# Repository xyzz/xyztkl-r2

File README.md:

# xyztkl rev2

*— Photos by [@kokaloo_](https://www.instagram.com/kokaloo_/)*

## License

CC0 apart from the switch footprints and component STEP models, see LICENSE.txt.

## Known issues

- The PCB is a bit hard to align inside the case
- The screw holes aren't at the same depth from the top

## Notes

- dboard: this uses a custom daughterboard; should be 1mm thick. JST cable or pinout **not** compatible with ai03 daughterboard
- pcb: the included PCB is using STM32F103 (or a compatible clone), you will need an ST-LINK to program the included bootloader; recommend matching the color to the color of the bottom piece if possible; should be 1.6mm thick
- jst cable: 100mm, reverse orientation (pins 1-4 on one side map to 4-1 on the other) - note that this is the opposite of what ai03 unified daughterboard uses, if you use a wrong cable you risk killing the pcb
- ALPS support: an alps-compatible PCB and plate files are provided, however they are designed to be used with the Tai Hao alps keyset and an MX spacebar; no compatibility for other layouts is provided

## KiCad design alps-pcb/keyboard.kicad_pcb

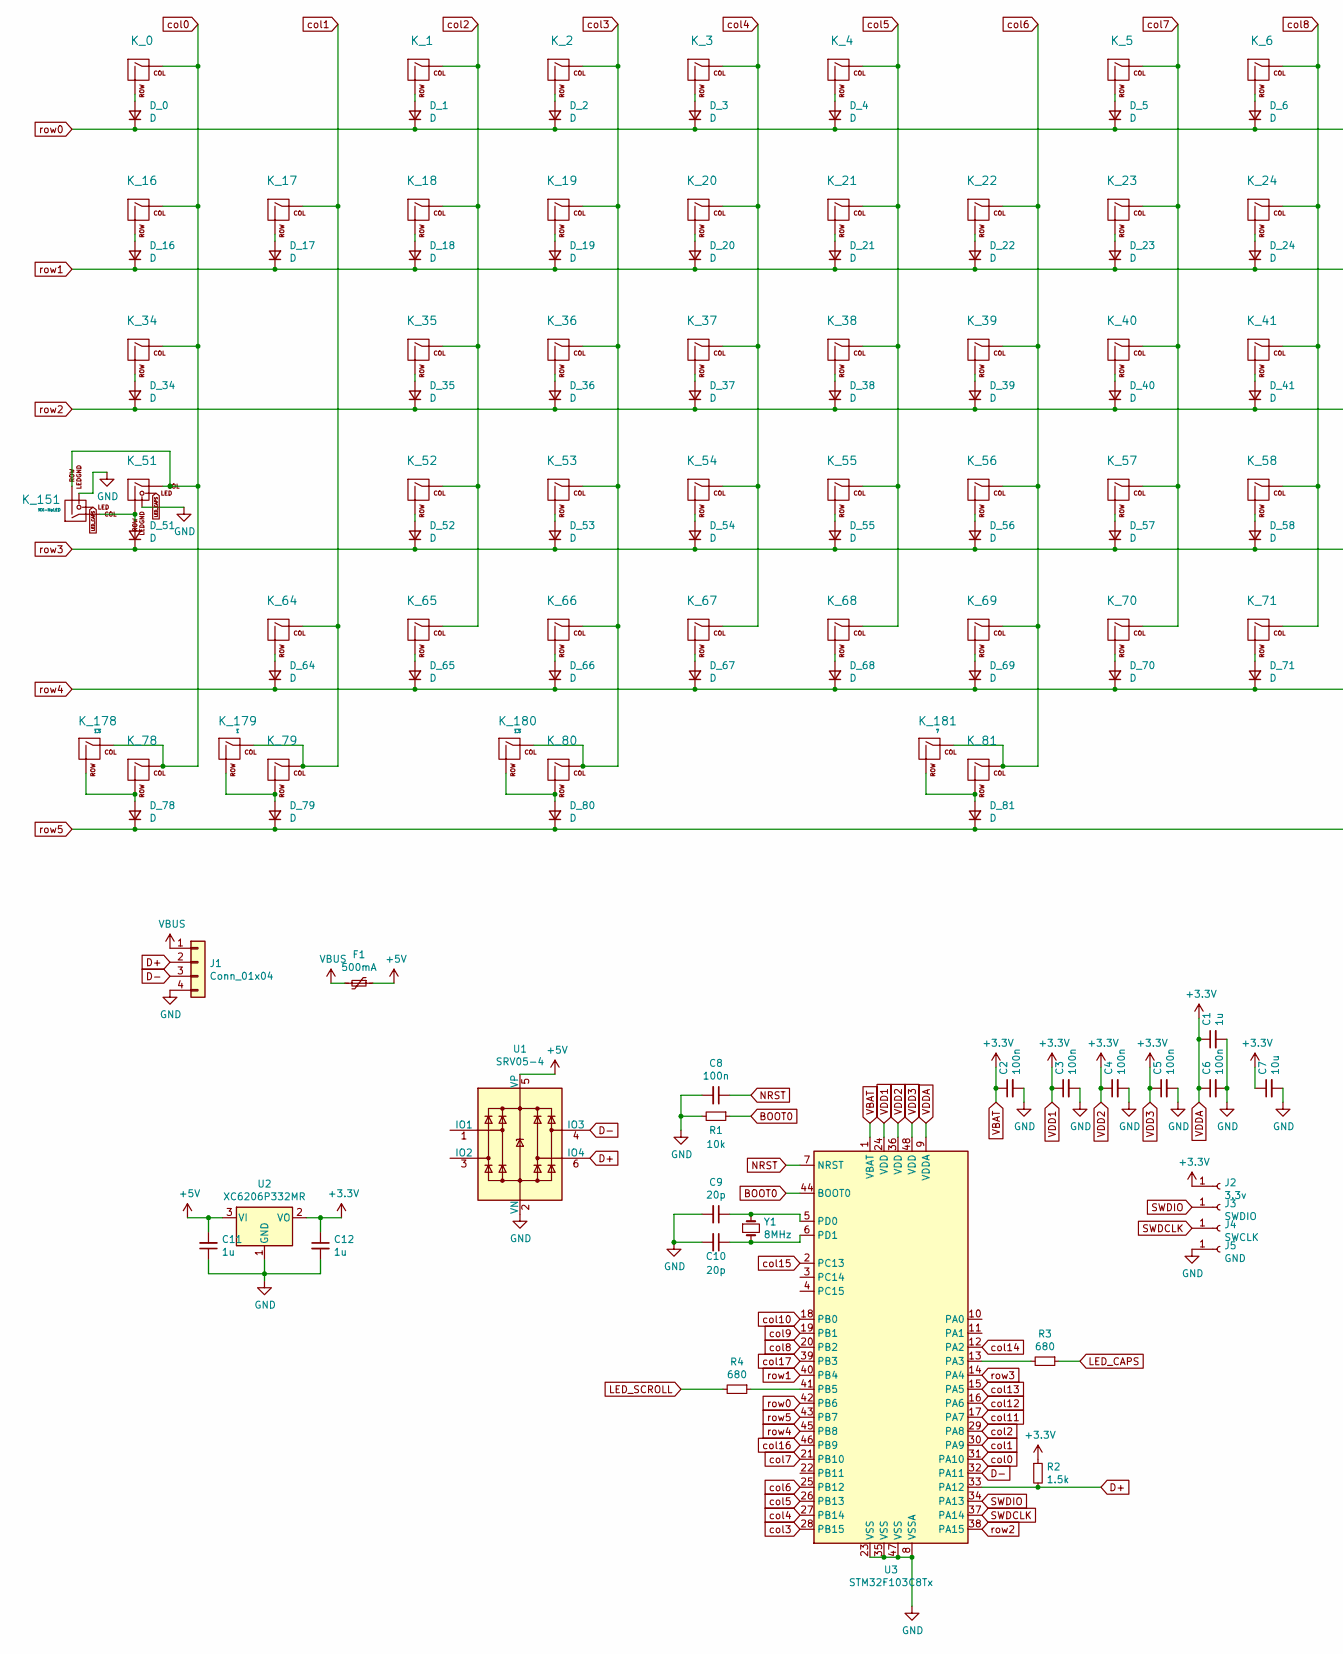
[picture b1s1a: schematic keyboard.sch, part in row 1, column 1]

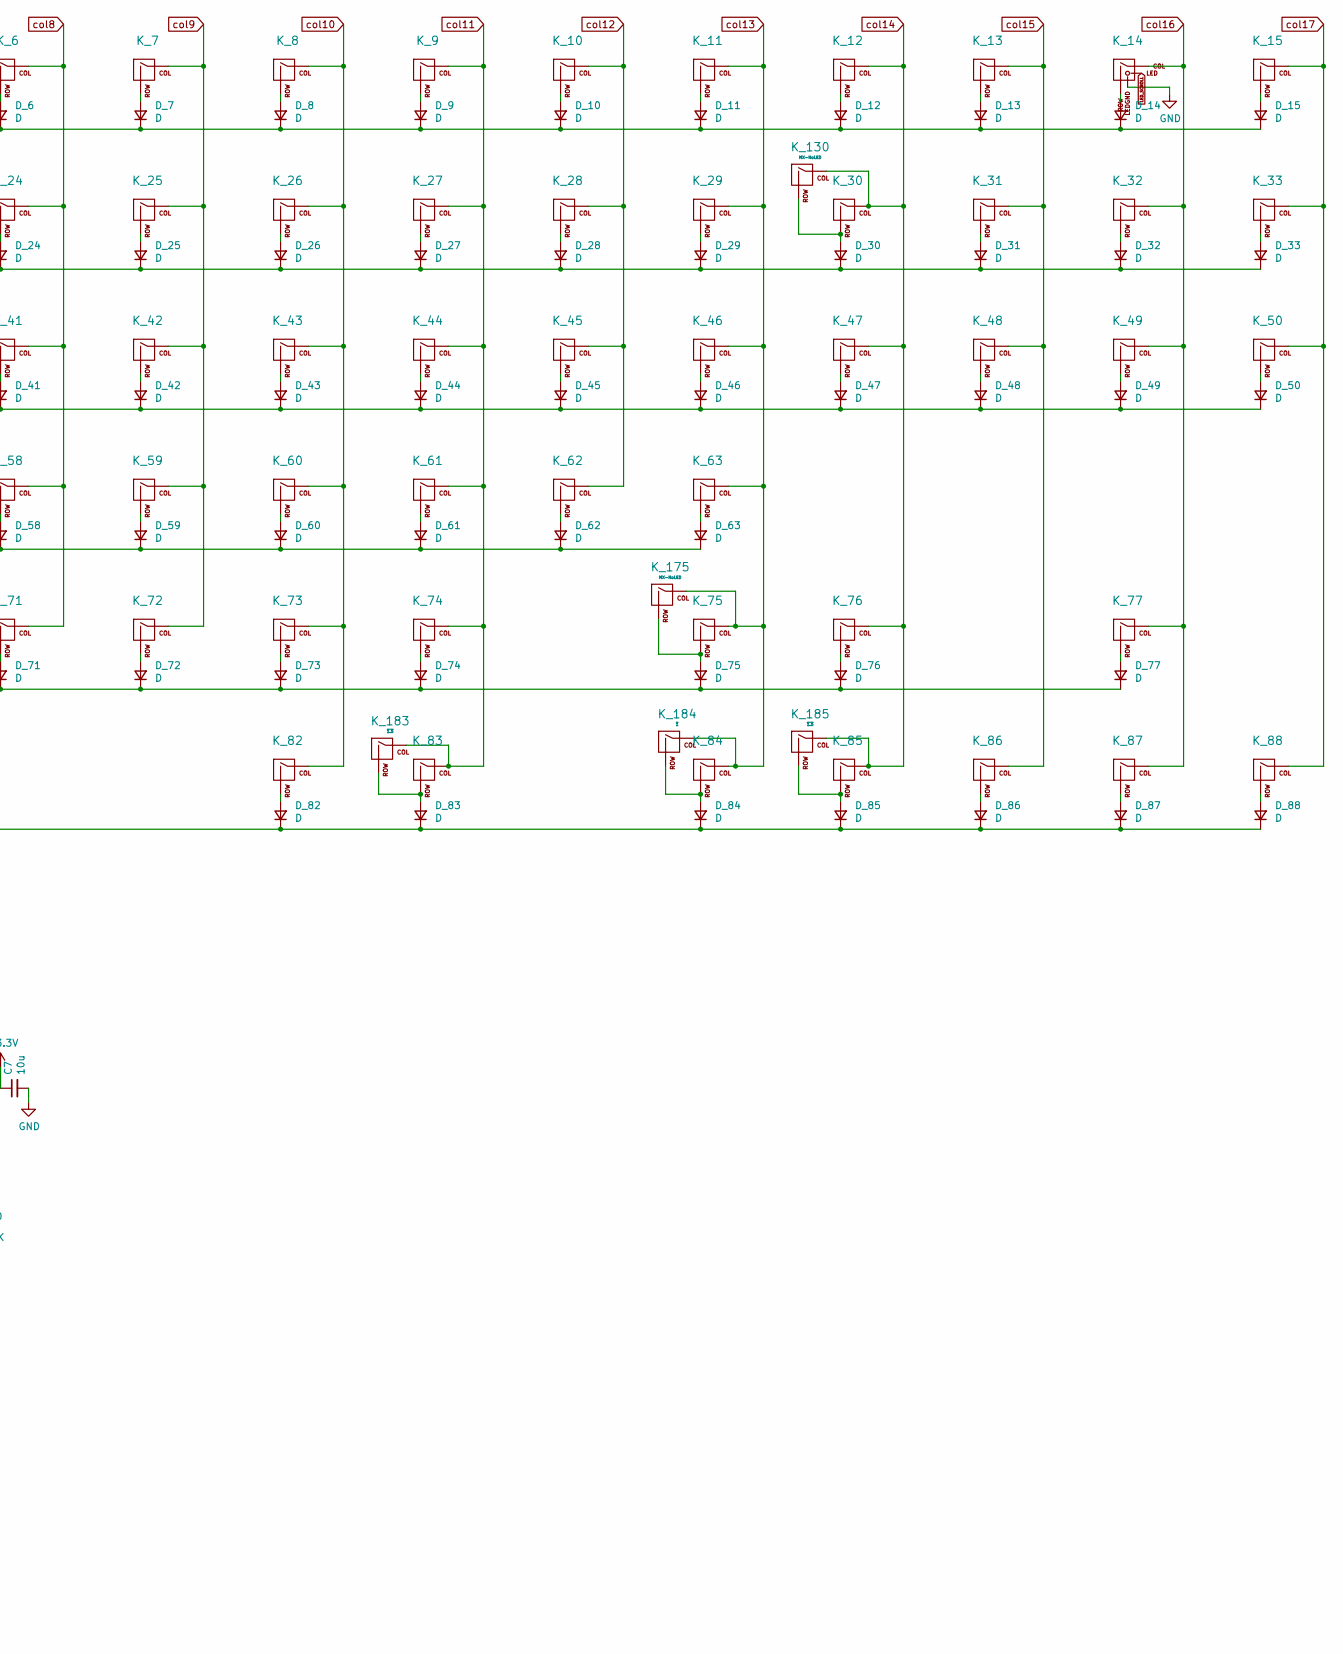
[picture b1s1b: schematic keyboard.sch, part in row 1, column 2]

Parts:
C1, C11, C12: 1u; C_0603_1608Metric; LCSC C15849
C2, C3, C4, C5, C6, C8: 100n; C_0603_1608Metric; LCSC C14663
C7: 10u; C_0603_1608Metric; LCSC C19702
C9, C10: 20p; C_0603_1608Metric; LCSC C1648
D_0, D_1, D_2, D_3, D_4, D_5, D_6, D_7, D_8, D_9, D_10, D_11, D_12, D_13, D_14, D_15, D_16, D_17, D_18, D_19, D_20, D_21, D_22, D_23, D_24, D_25, D_26, D_27, D_28, D_29, D_30, D_31, D_32, D_33, D_34, D_35, D_36, D_37, D_38, D_39, D_40, D_41, D_42, D_43, D_44, D_45, D_46, D_47, D_48, D_49, D_50, D_51, D_52, D_53, D_54, D_55, D_56, D_57, D_58, D_59, D_60, D_61, D_62, D_63, D_64, D_65, D_66, D_67, D_68, D_69, D_70, D_71, D_72, D_73, D_74, D_75, D_76, D_77, D_78, D_79, D_80, D_81, D_82, D_83, D_84, D_85, D_86, D_87, D_88: D; D_SOD-123; LCSC C81598
F1: 500mA; Fuse_1206_3216Metric; LCSC C369159
J1: Conn_01x04; JST_SH_SM04B-SRSS-TB_1x04-1MP_P1.00mm_Horizontal; LCSC C160404
J2: 3.3v; TestPoint_Pad_D1.5mm
J3: SWDIO; TestPoint_Pad_D1.5mm
J4: SWCLK; TestPoint_Pad_D1.5mm
J5: GND; TestPoint_Pad_D1.5mm
K_0, K_1, K_2, K_3, K_4, K_5, K_6, K_7, K_8, K_9, K_10, K_11, K_12, K_13, K_15, K_16, K_17, K_18, K_19, K_20, K_21, K_22, K_23, K_24, K_25, K_26, K_27, K_28, K_29, K_30, K_31, K_32, K_33, K_35, K_36, K_37, K_38, K_39, K_40, K_41, K_42, K_43, K_44, K_45, K_46, K_48, K_49, K_50, K_52, K_53, K_54, K_55, K_56, K_57, K_58, K_59, K_60, K_61, K_62, K_65, K_66, K_67, K_68, K_69, K_70, K_71, K_72, K_73, K_74, K_76, K_77, K_86, K_87, K_88: KEYSW; MX-1U-NoLED
K_14: KEYSW; MX-1U
K_34, K_47: KEYSW; MX-1.5U-NoLED
K_51: KEYSW; MX-1.75U
K_63, K_64: KEYSW; MX-2.25U-NoLED
K_75: KEYSW; MX-1.75U-NoLED
K_78, K_79, K_80, K_82, K_83, K_84, K_85: 1.25; MX-1.25U-NoLED
K_81: 6.25; MX-6.25U-ReversedStabilizers-NoLED
K_130: MX-NoLED; MX-2U-NoLED
K_151: MX-NoLED; MX-1.25U-FLIPPED
K_175: MX-NoLED; MX-2.75U-NoLED
K_178, K_180, K_183, K_185: ~1.5; MX-1.5U-NoLED
K_179, K_184: ~1; MX-1U-NoLED
K_181: ~7; MX-7U-ReversedStabilizers-NoLED
R1: 10k; R_0603_1608Metric; LCSC C25804
R2: 1.5k; R_0603_1608Metric; LCSC C22843
R3, R4: 680; R_0603_1608Metric; LCSC C23228
U1: SRV05-4; SOT-23-6; LCSC C85364
U2: XC6206P332MR; SOT-23; LCSC C5446
U3: STM32F103C8Tx; LQFP-48_7x7mm_P0.5mm
Y1: 8MHz; Crystal_SMD_5032-2Pin_5.0x3.2mm; LCSC C115962

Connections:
+5V: C11.2, F1.1, U1.5 (VP), U2.3 (VI)
BOOT0: R1.1, U3.44 (BOOT0)
D+: J1.2, R2.2, U1.6 (IO4), U3.33 (PA12)
D-: J1.3, U1.4 (IO3), U3.32 (PA11)
GND: C1.2, C2.2, C3.2, C4.2, C5.2, C6.2, C7.2, C8.2, C9.2, C10.2, C11.1, C12.2, J1.4, J5.1, K_14.4 (LEDGND), K_51.4 (LEDGND), K_151.4 (LEDGND), R1.2, U1.2 (VN), U2.1 (GND), U3.8 (VSSA), U3.23 (VSS), U3.35 (VSS), U3.47 (VSS)
LED_CAPS: K_51.3 (LED), K_151.3 (LED), R3.1
LED_SCROLL: K_14.3 (LED), R4.2
NRST: C8.1, U3.7 (NRST)
unnamed: C9.1, U3.5 (PD0), Y1.1
unnamed: C10.1, U3.6 (PD1), Y1.2
unnamed: D_0.2 (A), K_0.2 (ROW)
unnamed: D_1.2 (A), K_1.2 (ROW)
unnamed: D_2.2 (A), K_2.2 (ROW)
unnamed: D_3.2 (A), K_3.2 (ROW)
unnamed: D_4.2 (A), K_4.2 (ROW)
unnamed: D_5.2 (A), K_5.2 (ROW)
unnamed: D_6.2 (A), K_6.2 (ROW)
unnamed: D_7.2 (A), K_7.2 (ROW)
unnamed: D_8.2 (A), K_8.2 (ROW)
unnamed: D_9.2 (A), K_9.2 (ROW)
unnamed: D_10.2 (A), K_10.2 (ROW)
unnamed: D_11.2 (A), K_11.2 (ROW)
unnamed: D_12.2 (A), K_12.2 (ROW)
unnamed: D_13.2 (A), K_13.2 (ROW)
unnamed: D_14.2 (A), K_14.2 (ROW)
unnamed: D_15.2 (A), K_15.2 (ROW)
unnamed: D_16.2 (A), K_16.2 (ROW)
unnamed: D_17.2 (A), K_17.2 (ROW)
unnamed: D_18.2 (A), K_18.2 (ROW)
unnamed: D_19.2 (A), K_19.2 (ROW)
unnamed: D_20.2 (A), K_20.2 (ROW)
unnamed: D_21.2 (A), K_21.2 (ROW)
unnamed: D_22.2 (A), K_22.2 (ROW)
unnamed: D_23.2 (A), K_23.2 (ROW)
unnamed: D_24.2 (A), K_24.2 (ROW)
unnamed: D_25.2 (A), K_25.2 (ROW)
unnamed: D_26.2 (A), K_26.2 (ROW)
unnamed: D_27.2 (A), K_27.2 (ROW)
unnamed: D_28.2 (A), K_28.2 (ROW)
unnamed: D_29.2 (A), K_29.2 (ROW)
unnamed: D_30.2 (A), K_30.2 (ROW), K_130.2 (ROW)
unnamed: D_31.2 (A), K_31.2 (ROW)
unnamed: D_32.2 (A), K_32.2 (ROW)
unnamed: D_33.2 (A), K_33.2 (ROW)
unnamed: D_34.2 (A), K_34.2 (ROW)
unnamed: D_35.2 (A), K_35.2 (ROW)
unnamed: D_36.2 (A), K_36.2 (ROW)
unnamed: D_37.2 (A), K_37.2 (ROW)
unnamed: D_38.2 (A), K_38.2 (ROW)
unnamed: D_39.2 (A), K_39.2 (ROW)
unnamed: D_40.2 (A), K_40.2 (ROW)
unnamed: D_41.2 (A), K_41.2 (ROW)
unnamed: D_42.2 (A), K_42.2 (ROW)
unnamed: D_43.2 (A), K_43.2 (ROW)
unnamed: D_44.2 (A), K_44.2 (ROW)
unnamed: D_45.2 (A), K_45.2 (ROW)
unnamed: D_46.2 (A), K_46.2 (ROW)
unnamed: D_47.2 (A), K_47.2 (ROW)
unnamed: D_48.2 (A), K_48.2 (ROW)
unnamed: D_49.2 (A), K_49.2 (ROW)
unnamed: D_50.2 (A), K_50.2 (ROW)
unnamed: D_51.2 (A), K_51.2 (ROW), K_151.1 (COL)
unnamed: D_52.2 (A), K_52.2 (ROW)
unnamed: D_53.2 (A), K_53.2 (ROW)
unnamed: D_54.2 (A), K_54.2 (ROW)
unnamed: D_55.2 (A), K_55.2 (ROW)
unnamed: D_56.2 (A), K_56.2 (ROW)
unnamed: D_57.2 (A), K_57.2 (ROW)
unnamed: D_58.2 (A), K_58.2 (ROW)
unnamed: D_59.2 (A), K_59.2 (ROW)
unnamed: D_60.2 (A), K_60.2 (ROW)
unnamed: D_61.2 (A), K_61.2 (ROW)
unnamed: D_62.2 (A), K_62.2 (ROW)
unnamed: D_63.2 (A), K_63.2 (ROW)
unnamed: D_64.2 (A), K_64.2 (ROW)
unnamed: D_65.2 (A), K_65.2 (ROW)
unnamed: D_66.2 (A), K_66.2 (ROW)
unnamed: D_67.2 (A), K_67.2 (ROW)
unnamed: D_68.2 (A), K_68.2 (ROW)
unnamed: D_69.2 (A), K_69.2 (ROW)
unnamed: D_70.2 (A), K_70.2 (ROW)
unnamed: D_71.2 (A), K_71.2 (ROW)
unnamed: D_72.2 (A), K_72.2 (ROW)
unnamed: D_73.2 (A), K_73.2 (ROW)
unnamed: D_74.2 (A), K_74.2 (ROW)
unnamed: D_75.2 (A), K_75.2 (ROW), K_175.2 (ROW)
unnamed: D_76.2 (A), K_76.2 (ROW)
unnamed: D_77.2 (A), K_77.2 (ROW)
unnamed: D_78.2 (A), K_78.2 (ROW), K_178.2 (ROW)
unnamed: D_79.2 (A), K_79.2 (ROW), K_179.2 (ROW)
unnamed: D_80.2 (A), K_80.2 (ROW), K_180.2 (ROW)
unnamed: D_81.2 (A), K_81.2 (ROW), K_181.2 (ROW)
unnamed: D_82.2 (A), K_82.2 (ROW)
unnamed: D_83.2 (A), K_83.2 (ROW), K_183.2 (ROW)
unnamed: D_84.2 (A), K_84.2 (ROW), K_184.2 (ROW)
unnamed: D_85.2 (A), K_85.2 (ROW), K_185.2 (ROW)
unnamed: D_86.2 (A), K_86.2 (ROW)
unnamed: D_87.2 (A), K_87.2 (ROW)
unnamed: D_88.2 (A), K_88.2 (ROW)
unnamed: R3.2, U3.13 (PA3)
unnamed: R4.1, U3.41 (PB5)
SWDCLK: J4.1, U3.37 (PA14)
SWDIO: J3.1, U3.34 (PA13)
VBAT: C1.1, C2.1, C3.1, C4.1, C5.1, C6.1, C7.1, C12.1, J2.1, R2.1, U2.2 (VO), U3.1 (VBAT), U3.9 (VDDA), U3.24 (VDD), U3.36 (VDD), U3.48 (VDD)
VBUS: F1.2, J1.1
col0: K_0.1 (COL), K_16.1 (COL), K_34.1 (COL), K_51.1 (COL), K_78.1 (COL), K_151.2 (ROW), K_178.1 (COL), U3.31 (PA10)
col1: K_17.1 (COL), K_64.1 (COL), K_79.1 (COL), K_179.1 (COL), U3.30 (PA9)
col2: K_1.1 (COL), K_18.1 (COL), K_35.1 (COL), K_52.1 (COL), K_65.1 (COL), U3.29 (PA8)
col3: K_2.1 (COL), K_19.1 (COL), K_36.1 (COL), K_53.1 (COL), K_66.1 (COL), K_80.1 (COL), K_180.1 (COL), U3.28 (PB15)
col4: K_3.1 (COL), K_20.1 (COL), K_37.1 (COL), K_54.1 (COL), K_67.1 (COL), U3.27 (PB14)
col5: K_4.1 (COL), K_21.1 (COL), K_38.1 (COL), K_55.1 (COL), K_68.1 (COL), U3.26 (PB13)
col6: K_22.1 (COL), K_39.1 (COL), K_56.1 (COL), K_69.1 (COL), K_81.1 (COL), K_181.1 (COL), U3.25 (PB12)
col7: K_5.1 (COL), K_23.1 (COL), K_40.1 (COL), K_57.1 (COL), K_70.1 (COL), U3.21 (PB10)
col8: K_6.1 (COL), K_24.1 (COL), K_41.1 (COL), K_58.1 (COL), K_71.1 (COL), U3.20 (PB2)
col9: K_7.1 (COL), K_25.1 (COL), K_42.1 (COL), K_59.1 (COL), K_72.1 (COL), U3.19 (PB1)
col10: K_8.1 (COL), K_26.1 (COL), K_43.1 (COL), K_60.1 (COL), K_73.1 (COL), K_82.1 (COL), U3.18 (PB0)
col11: K_9.1 (COL), K_27.1 (COL), K_44.1 (COL), K_61.1 (COL), K_74.1 (COL), K_83.1 (COL), K_183.1 (COL), U3.17 (PA7)
col12: K_10.1 (COL), K_28.1 (COL), K_45.1 (COL), K_62.1 (COL), U3.16 (PA6)
col13: K_11.1 (COL), K_29.1 (COL), K_46.1 (COL), K_63.1 (COL), K_75.1 (COL), K_84.1 (COL), K_175.1 (COL), K_184.1 (COL), U3.15 (PA5)
col14: K_12.1 (COL), K_30.1 (COL), K_47.1 (COL), K_76.1 (COL), K_85.1 (COL), K_130.1 (COL), K_185.1 (COL), U3.12 (PA2)
col15: K_13.1 (COL), K_31.1 (COL), K_48.1 (COL), K_86.1 (COL), U3.2 (PC13)
col16: K_14.1 (COL), K_32.1 (COL), K_49.1 (COL), K_77.1 (COL), K_87.1 (COL), U3.46 (PB9)
col17: K_15.1 (COL), K_33.1 (COL), K_50.1 (COL), K_88.1 (COL), U3.39 (PB3)
row0: D_0.1 (K), D_1.1 (K), D_2.1 (K), D_3.1 (K), D_4.1 (K), D_5.1 (K), D_6.1 (K), D_7.1 (K), D_8.1 (K), D_9.1 (K), D_10.1 (K), D_11.1 (K), D_12.1 (K), D_13.1 (K), D_14.1 (K), D_15.1 (K), U3.42 (PB6)
row1: D_16.1 (K), D_17.1 (K), D_18.1 (K), D_19.1 (K), D_20.1 (K), D_21.1 (K), D_22.1 (K), D_23.1 (K), D_24.1 (K), D_25.1 (K), D_26.1 (K), D_27.1 (K), D_28.1 (K), D_29.1 (K), D_30.1 (K), D_31.1 (K), D_32.1 (K), D_33.1 (K), U3.40 (PB4)
row2: D_34.1 (K), D_35.1 (K), D_36.1 (K), D_37.1 (K), D_38.1 (K), D_39.1 (K), D_40.1 (K), D_41.1 (K), D_42.1 (K), D_43.1 (K), D_44.1 (K), D_45.1 (K), D_46.1 (K), D_47.1 (K), D_48.1 (K), D_49.1 (K), D_50.1 (K), U3.38 (PA15)
row3: D_51.1 (K), D_52.1 (K), D_53.1 (K), D_54.1 (K), D_55.1 (K), D_56.1 (K), D_57.1 (K), D_58.1 (K), D_59.1 (K), D_60.1 (K), D_61.1 (K), D_62.1 (K), D_63.1 (K), U3.14 (PA4)
row4: D_64.1 (K), D_65.1 (K), D_66.1 (K), D_67.1 (K), D_68.1 (K), D_69.1 (K), D_70.1 (K), D_71.1 (K), D_72.1 (K), D_73.1 (K), D_74.1 (K), D_75.1 (K), D_76.1 (K), D_77.1 (K), U3.45 (PB8)
row5: D_78.1 (K), D_79.1 (K), D_80.1 (K), D_81.1 (K), D_82.1 (K), D_83.1 (K), D_84.1 (K), D_85.1 (K), D_86.1 (K), D_87.1 (K), D_88.1 (K), U3.43 (PB7)

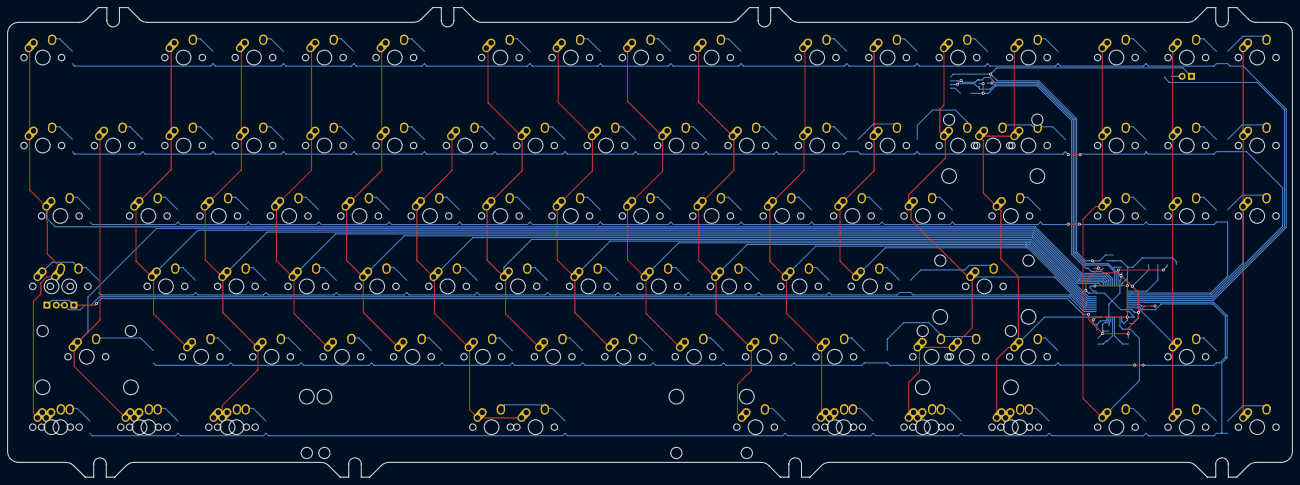
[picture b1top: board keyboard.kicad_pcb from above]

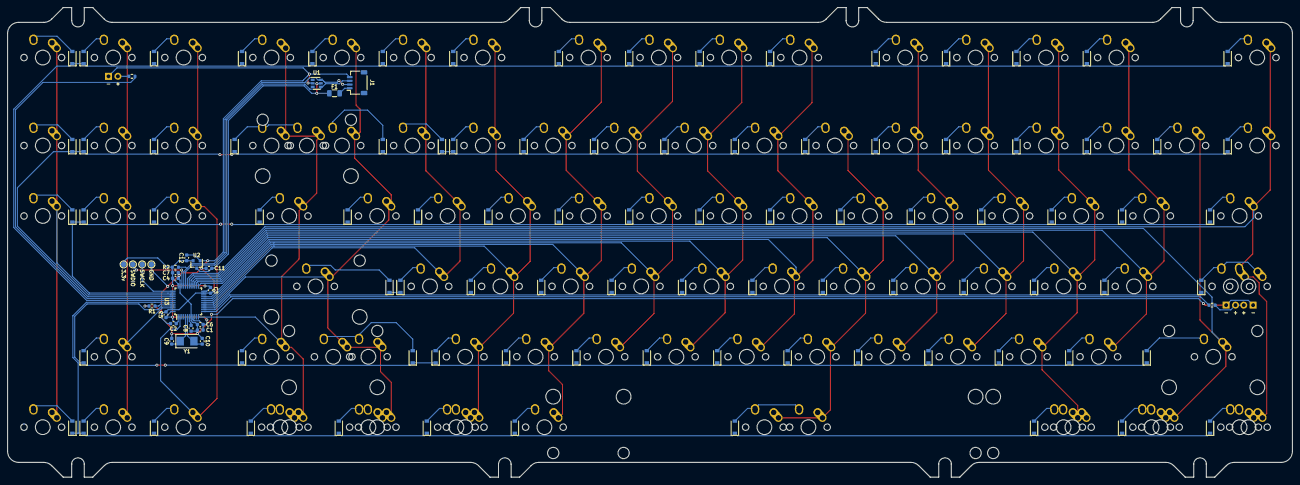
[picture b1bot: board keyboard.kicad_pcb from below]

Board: 2 copper layers, 347.7 x 127.1 mm, 214 parts (115 on the bottom side), 129 nets.

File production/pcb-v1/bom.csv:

Comment,Designator,Footprint,LCSC
KEYSW,"K_0,K_1,K_2,K_3,K_4,K_5,K_6,K_7,K_8,K_9,K_10,K_11,K_12,K_13,K_15,K_16,K_17,K_18,K_19,K_20,K_21,K_22,K_23,K_24,K_25,K_26,K_27,K_28,K_29,K_30,K_31,K_32,K_33,K_35,K_36,K_37,K_38,K_39,K_40,K_41,K_42,K_43,K_44,K_45,K_46,K_48,K_49,K_50,K_52,K_53,K_54,K_55,K_56,K_57,K_58,K_59,K_60,K_61,K_62,K_65,K_66,K_67,K_68,K_69,K_70,K_71,K_72,K_73,K_74,K_76,K_77,K_86,K_87,K_88",MX_Only:MXOnly-1U-NoLED,
D,"D_0,D_1,D_2,D_3,D_4,D_5,D_6,D_7,D_8,D_9,D_10,D_11,D_12,D_13,D_14,D_15,D_16,D_17,D_18,D_19,D_20,D_21,D_22,D_23,D_24,D_25,D_26,D_27,D_28,D_29,D_30,D_31,D_32,D_33,D_34,D_35,D_36,D_37,D_38,D_39,D_40,D_41,D_42,D_43,D_44,D_45,D_46,D_47,D_48,D_49,D_50,D_51,D_52,D_53,D_54,D_55,D_56,D_57,D_58,D_59,D_60,D_61,D_62,D_63,D_64,D_65,D_66,D_67,D_68,D_69,D_70,D_71,D_72,D_73,D_74,D_75,D_76,D_77,D_78,D_79,D_80,D_81,D_82,D_83,D_84,D_85,D_86,D_87,D_88",Diode_SMD:D_SOD-123,C81598
KEYSW,K_14,MX_Only:MXOnly-1U,
KEYSW,"K_34,K_47",MX_Only:MXOnly-1.5U-NoLED,
KEYSW,K_51,MX_Only:MXOnly-1.75U,
KEYSW,"K_63,K_64",MX_Only:MXOnly-2.25U-NoLED,
KEYSW,K_75,MX_Only:MXOnly-1.75U-NoLED,
1.25,"K_78,K_79,K_80,K_82,K_83,K_84,K_85",MX_Only:MXOnly-1.25U-NoLED,
6.25,K_81,MX_Only:MXOnly-6.25U-ReversedStabilizers-NoLED,
~7,K_181,MX_Only:MXOnly-7U-ReversedStabilizers-NoLED,
~1.5,"K_178,K_180,K_183,K_185",MX_Only:MXOnly-1.5U-NoLED,
~1,"K_179,K_184",MX_Only:MXOnly-1U-NoLED,
Conn_01x04,J1,Connector_JST:JST_SH_SM04B-SRSS-TB_1x04-1MP_P1.00mm_Horizontal,C160404
MX-NoLED,K_175,MX_Only:MXOnly-2.75U-NoLED,
MX-NoLED,K_130,MX_Only:MXOnly-2U-NoLED,
8MHz,Y1,Crystal:Crystal_SMD_5032-2Pin_5.0x3.2mm,C115962
20p,"C9,C10",Capacitor_SMD:C_0603_1608Metric,C1648
10u,C7,Capacitor_SMD:C_0603_1608Metric,C19702
100n,"C2,C3,C4,C5,C6,C8",Capacitor_SMD:C_0603_1608Metric,C14663
10k,R1,Resistor_SMD:R_0603_1608Metric,C25804
STM32F103C8Tx,U3,Package_QFP:LQFP-48_7x7mm_P0.5mm,
1u,"C1,C12,C11",Capacitor_SMD:C_0603_1608Metric,C15849
SWDIO,J3,TestPoint:TestPoint_Pad_D1.5mm,
SWCLK,J4,TestPoint:TestPoint_Pad_D1.5mm,
GND,J5,TestPoint:TestPoint_Pad_D1.5mm,
XC6206P332MR,U2,Package_TO_SOT_SMD:SOT-23,C5446
500mA,F1,Fuse:Fuse_1206_3216Metric,C369159
1.5k,R2,Resistor_SMD:R_0603_1608Metric,C22843
3.3v,J2,TestPoint:TestPoint_Pad_D1.5mm,
SRV05-4,U1,Package_TO_SOT_SMD:SOT-23-6,C85364
MX-NoLED,K_151,MX_Only:MXOnly-1.25U-FLIPPED,
680,"R3,R4",Resistor_SMD:R_0603_1608Metric,C23228

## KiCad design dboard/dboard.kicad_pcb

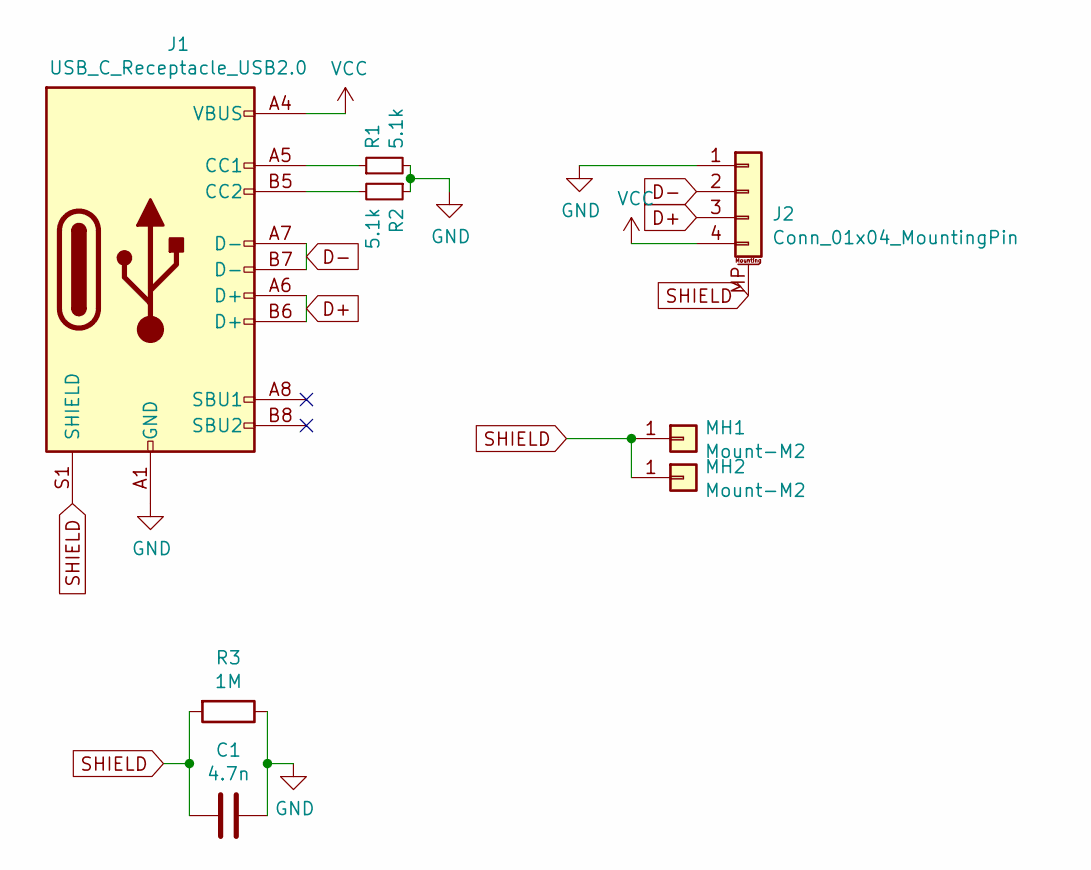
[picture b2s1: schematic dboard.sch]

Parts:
C1: 4.7n; C_0603_1608Metric; LCSC C53987
J1: USB_C_Receptacle_USB2.0; USB_C_Receptacle_HRO_TYPE-C-31-M-12; LCSC C165948
J2: Conn_01x04_MountingPin; JST_SH_SM04B-SRSS-TB_1x04-1MP_P1.00mm_Horizontal; LCSC C160404
MH1, MH2: Mount-M2; MountingHole_3.2mm_M3_Pad_Via
R1, R2: 5.1k; R_0603_1608Metric; LCSC C23186
R3: 1M; R_0805_2012Metric; LCSC C17514

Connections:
D+: J1.A6 (D+), J1.B6 (D+), J2.3
D-: J1.A7 (D-), J1.B7 (D-), J2.2
GND: C1.1, J1.A1 (GND), J1.A12 (GND), J1.B1 (GND), J1.B12 (GND), J2.1, R1.2, R2.1, R3.1
unnamed: J1.A5 (CC1), R1.1
unnamed: J1.B5 (CC2), R2.2
SHIELD: C1.2, J1.S1 (SHIELD), J2.MP (MountPin), MH1.1, MH2.1, R3.2
VCC: J1.A4 (VBUS), J1.A9 (VBUS), J1.B4 (VBUS), J1.B9 (VBUS), J2.4

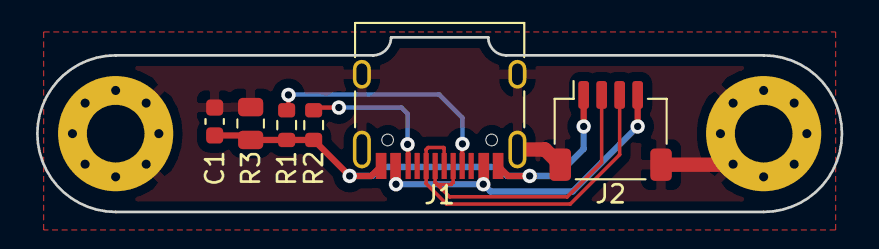
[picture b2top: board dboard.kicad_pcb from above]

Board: 2 copper layers, 44.7 x 9.7 mm, 8 parts (0 on the bottom side), 7 nets.

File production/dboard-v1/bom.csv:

Comment,Designator,Footprint,LCSC
5.1k,"R2,R1",Resistor_SMD:R_0603_1608Metric,C23186
Mount-M2,"MH1,MH2",MountingHole:MountingHole_3.2mm_M3_Pad_Via,
1M,R3,Resistor_SMD:R_0805_2012Metric,C17514
4.7n,C1,Capacitor_SMD:C_0603_1608Metric,C53987
USB_C_Receptacle_USB2.0,J1,Connector_USB:USB_C_Receptacle_HRO_TYPE-C-31-M-12,C165948
Conn_01x04_MountingPin,J2,Connector_JST:JST_SH_SM04B-SRSS-TB_1x04-1MP_P1.00mm_Horizontal,C160404

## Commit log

2022-03-13 initial
2022-03-13 add alps plate and pcb
